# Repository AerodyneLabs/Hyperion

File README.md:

Hyperion
========

Hardware and firmware for the Hyperion motherboard. Compatible with CubeSat kit standard.

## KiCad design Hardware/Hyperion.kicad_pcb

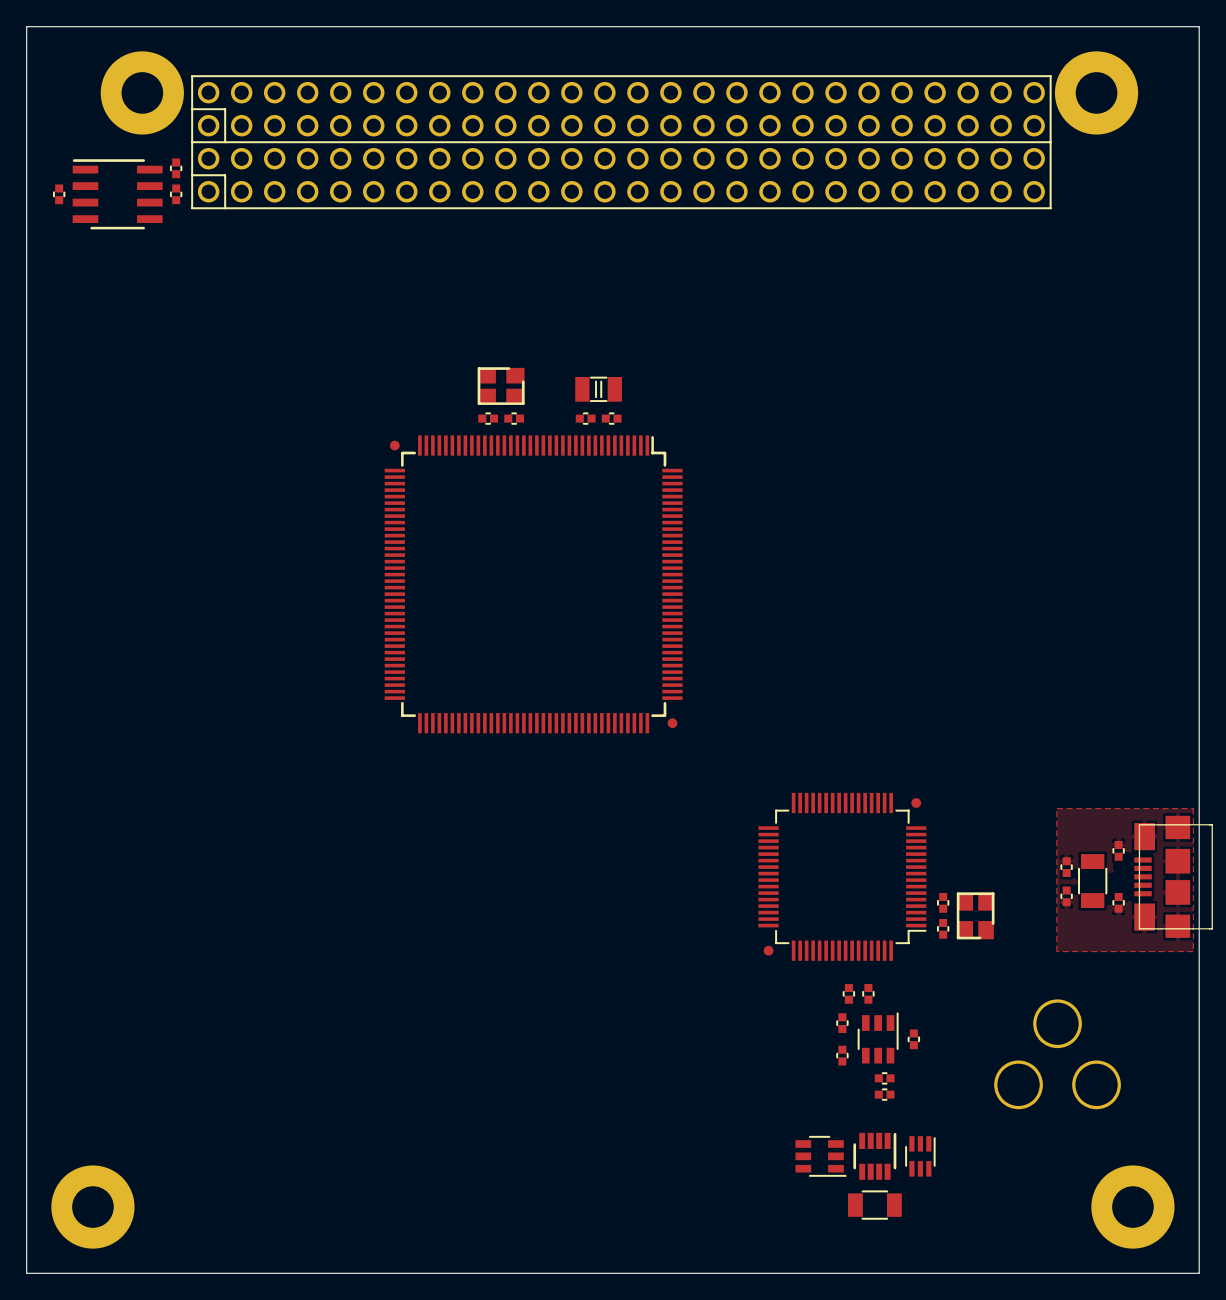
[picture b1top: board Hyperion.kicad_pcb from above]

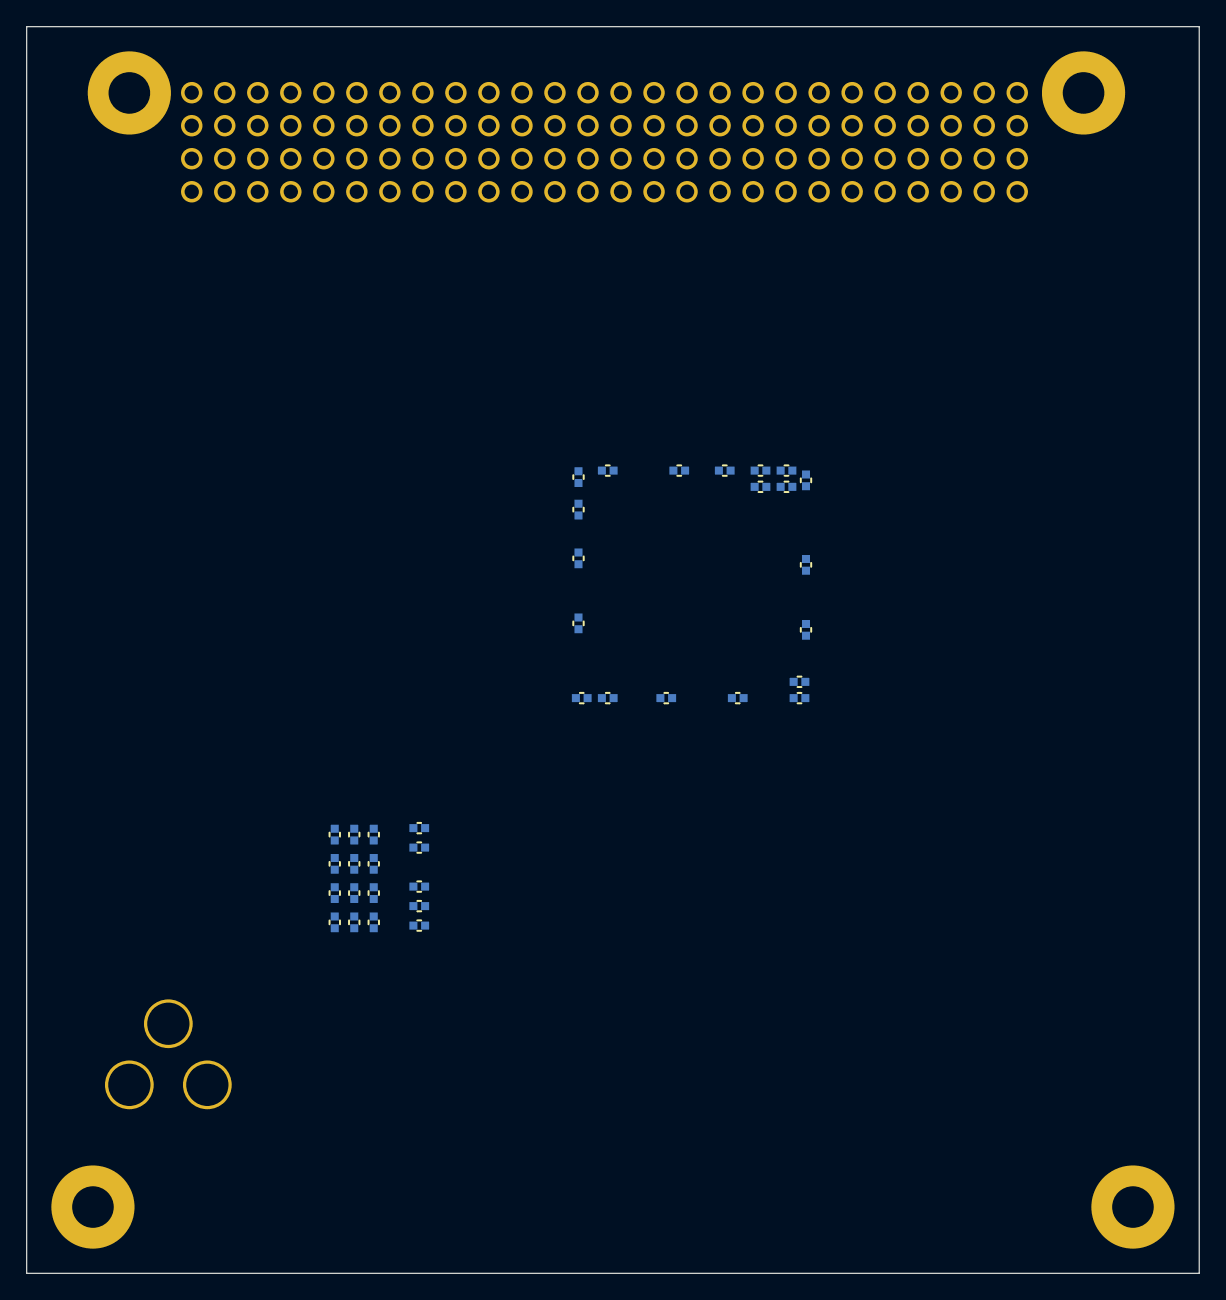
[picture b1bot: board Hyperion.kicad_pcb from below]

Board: 4 copper layers, 90.2 x 95.9 mm, 72 parts (37 on the bottom side), 53 nets, no tracks yet.

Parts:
C1, C3, C6, C32: 3.3uF; CAPC1005-N
C2, C4, C5, C7, C8, C9, C10, C12, C13, C15, C16, C19, C20, C21, C22, C23, C24, C25, C26, C27, C28, C29, C30, C31, C37, C38, C40: 0.1uF; CAPC1005-N
C11, C14, C33, C34, C35, C36: 10pF; CAPC1005-N
C17, C18: 2.2uF; CAPC1005-N
D1, D2: TVS; CAPC1005-N
FB1, FB2: 600; INDC1005-N
FB3: FERRITE; INDC1005-N
H1: CUBESAT-BUS
J1: USB; CONN-USB-MICRO-B-FCI
J2: CONN-DC; CONN-DC-CUI-202
Q1: MOSFET-P; SOT65P210-DDGSDD-N
Q2: FDC6561; SOT95P280-6N
R1, R2: MOV; RESC1005-N
R3: 12k; RESC1005-N
R4, R5, R6, R8, R9, R10, R12, R13: 10k; RESC1005-N
R7: 2.2k; RESC1005-N
R11: 0.02; RESC3216-N
R14: 120; RESC1005-N
TH1: PTC; RESC3216-N
U1: FT2232H; QFP50P1200X1200-64N
U2: 93LC46/OT; SOT95P280-6N
U3: LTC4361-T; SOT65P280-8N
U4: STM32F407ZE; QFP50P2200X2200-144N
U5: SN65HVD233; SOIC127P600-8N
X1, X2: 12MHz; XTAL-4SMD-32X25
X3: 32.768kHz; XTAL-2SMD-32x15

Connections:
+1.8V: C6.1, C12.1, C13.1, C16.1, U1.12, U1.37, U1.49, U1.64
+3.3V: C5.1, C7.1, C8.1, C9.1, C10.1, C15.1, C22.1, C23.1, C24.1, C25.1, C26.1, C27.1, C28.1, C29.1, C30.1, C31.1, C37.1, C38.1, C40.1, FB1.2, FB2.2, FB3.2, R4.2, R8.2, R9.2, R10.2, U1.20, U1.31, U1.42, U1.50, U1.56, U2.6, U4.17, U4.30, U4.39, U4.52, U4.62, U4.72, U4.84, U4.95, U4.108, U4.121, U4.131, U4.144, U5.3
+3.3VP: H1.2.27, H1.2.28
+5VP: H1.2.25, H1.2.26
+BATT: H1.2.45, H1.2.46
/Core/CANH: H1.1.3, R14.2, U5.7
/Core/CANL: H1.1.1, R14.1, U5.6
/Core/OSC0: C33.1, U4.23, X2.1
/Core/OSC1: C35.1, U4.24, X2.2
/Core/RST: C20.1, U4.25
/Core/TCK: U1.16, U4.109
/Core/TDI: U1.17, U4.110
/Core/TDO: U1.18, U4.133
/Core/TMS: U1.19, U4.105
/Core/XOSC0: C34.1, U4.8, X3.1
/Core/XOSC1: C36.1, U4.9, X3.2
/CubeSat Bus/S0: H1.2.33, H1.2.34
/CubeSat Bus/S1: H1.2.35, H1.2.36
/CubeSat Bus/S2: H1.2.37, H1.2.38
/CubeSat Bus/S3: H1.2.39, H1.2.40
/CubeSat Bus/S4: H1.2.41, H1.2.42
/CubeSat Bus/S5: H1.2.43, H1.2.44
/Interface Port/CLK: R8.1, U1.62, U2.4
/Interface Port/CS: R4.1, U1.63, U2.5
/Interface Port/D+: D2.2, J1.3, U1.8
/Interface Port/D-: D1.2, J1.2, U1.7
/Interface Port/DAT: R7.1, U1.61, U2.3
/Interface Port/OSCI: C11.1, U1.2, X1.1
/Interface Port/OSCO: C14.1, U1.3, X1.2
/Interface Port/PwrSav: R5.1, R6.2, U1.59
/Interface Port/Reset: R9.1, U1.14
/Interface Port/Shield: D1.1, D2.1, J1.S, R1.1, R2.1
DGND: H1.2.29, H1.2.30, H1.2.32
GND: C1.2, C2.2, C3.2, C4.2, C5.2, C6.2, C7.2, C8.2, C9.2, C10.2, C11.2, C12.2, C13.2, C14.2, C15.2, C16.2, C17.2, C18.2, C19.2, C20.2, C21.2, C22.2, C23.2, C24.2, C25.2, C26.2, C27.2, C28.2, C29.2, C30.2, C31.2, C32.2, C33.2, C34.2, C35.2, C36.2, C37.2, C38.2, C40.2, J1.5, R2.2, R3.1, R6.1, R12.1, U1.1, U1.5, U1.10, U1.11, U1.13, U1.15, U1.25, U1.35, U1.47, U1.51, U2.2, U3.1, U3.4, U4.16, U4.31, U4.38, U4.51, U4.61, U4.83, U4.94, U4.107, U4.120, U4.130, U5.2, U5.5
unnamed: Q2.1, Q2.3, U3.7
unnamed: Q1.S, R11.1, U3.5
unnamed: J2.1, Q1.D
unnamed: Q2.6, R11.2, U3.6
unnamed: Q1.G, U3.3
unnamed: Q2.4, U3.2
unnamed: Q2.2, Q2.5
unnamed: R3.2, U1.6
unnamed: J1.1, R1.2, TH1.2
unnamed: C3.1, C4.1, FB2.1, U1.4
unnamed: C1.1, C2.1, FB1.1, U1.9
unnamed: R7.2, R10.1, U2.1
unnamed: R13.2, U5.8
unnamed: R12.2, U4.138
unnamed: C17.1, U4.106
unnamed: C18.1, U4.71
unnamed: C21.1, C32.1, FB3.1, U4.33
VCOM: H1.1.32, R5.2, TH1.1
VMEM: C19.1, H1.1.42, U4.6

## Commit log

2013-10-08 Add hardware files
    Restructure repository to allow firmware and hardware. Update readme to
    reflect this. Add kicad to gitignore.
2013-10-08 Add pin map planning document
    Add Documentation directory.
2013-10-08 Add sample Eclipse project
    Add eclipse build files to gitignore
2013-10-10 Update project configuration
    Add predefiend symbols to support ROM mapping. Remove blinky.c
    test file. Add Debug directory to .gitignore.
2013-10-13 Add core components
2014-02-15 Add bus pinout
2014-02-15 Annotate and netlist
2014-02-15 Component association
2014-02-15 Core layout
2014-02-15 Save annotation
2014-02-17 Add dual channel FTDI
2014-02-26 Start fresh
2014-02-26 Preliminary spacecraft bus
2014-02-28 Rough USB interface
2014-03-02 Interface Component selection
2014-03-02 Temporary annotation
2014-03-02 Temporary associations
2014-03-04 Add protection circuit to DC jack
2014-03-12 Core support circuitry
2014-03-13 Rough layout
2014-03-15 Testing bottom side decoupling
2014-03-16 Add CAN transceiver
2014-03-17 Switch to STM32F4 MCU
2014-04-01 Clear core in prep for new MCU
2014-04-29 Rough pinout
2014-04-29 Starting CubeMX pinout/firmware
2014-05-01 Add support components
2014-05-01 Update clock frequencies in CubeMX
2014-05-02 Add SD card to core
2014-05-02 Add secondary oscillator
2014-05-04 Add RBF switch prototype
